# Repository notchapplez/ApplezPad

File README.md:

# ApplezPad

## PCB
Schematic

PCB

cat i drew myself, i am very proud .-.

I use kmk for the firmware.

I am just planning to mount my hackpad on this plate and it having a "naked" look.

## BOM:
- 9x Cherry MX Switches
- 6x DSA Keycaps
- 1x XIAO RP2040

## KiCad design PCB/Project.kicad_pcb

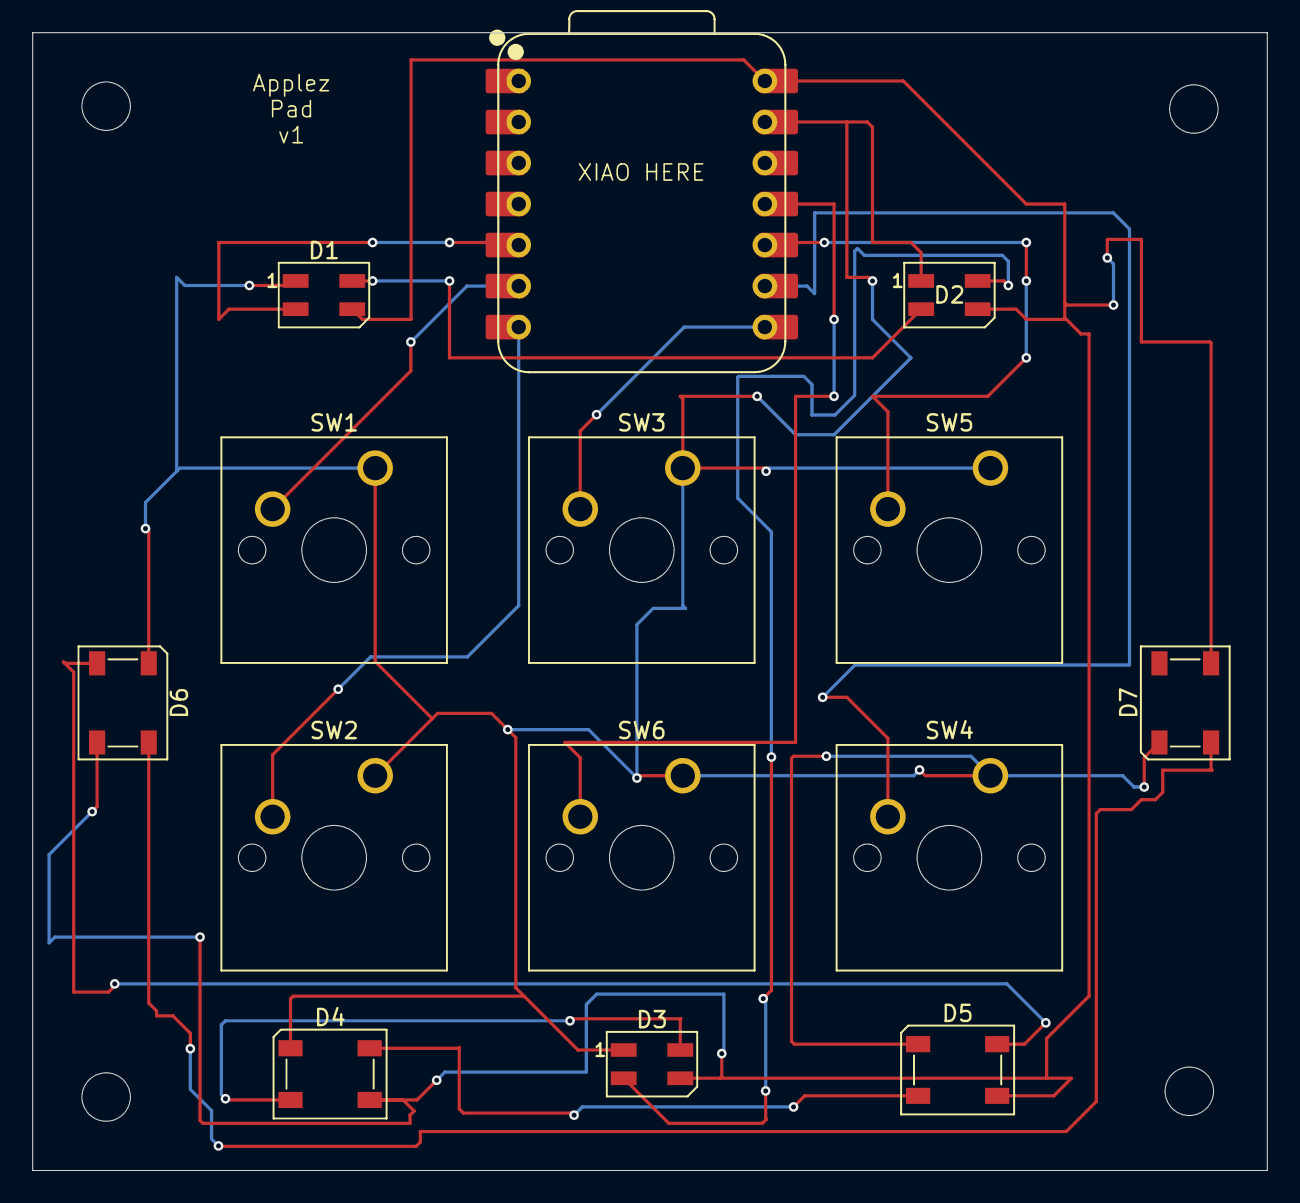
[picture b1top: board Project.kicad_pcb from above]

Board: 2 copper layers, 76.5 x 70.5 mm, 14 parts (0 on the bottom side), 15 nets.

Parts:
D1, D2, D3: SK6812; LED_SK6812MINI_PLCC4_3.5x3.5mm_P1.75mm
D4, D5, D6, D7: SK6812; LED_SK6812_PLCC4_5.0x5.0mm_P3.2mm
SW1, SW2, SW3, SW4, SW5, SW6: SW_Push; SW_Cherry_MX_1.00u_PCB
U1: XIAO-RP2040-DIP

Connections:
+5V: D1.3 (VDD), D2.3 (VDD), D3.3 (VDD), D4.3 (VDD), D5.3 (VDD), D6.3 (VDD), D7.3 (VDD), U1.14 (VBUS)
GND: D1.1 (VSS), D2.1 (VSS), D3.1 (VSS), D4.1 (VSS), D5.1 (VSS), D6.1 (VSS), D7.1 (VSS), SW1.1, SW2.1, SW3.1, SW4.1, SW5.1, SW6.1, U1.13 (GND)
unnamed: D1.2 (DIN), U1.5 (GPIO6/SDA)
unnamed: D1.4 (DOUT), D2.2 (DIN)
unnamed: D2.4 (DOUT), D3.2 (DIN)
unnamed: D3.4 (DOUT), D4.2 (DIN)
unnamed: D4.4 (DOUT), D5.2 (DIN)
unnamed: D5.4 (DOUT), D6.2 (DIN)
unnamed: D6.4 (DOUT), D7.2 (DIN)
unnamed: SW2.2, U1.7 (GPIO0/TX)
unnamed: SW3.2, U1.8 (GPIO1/RX)
unnamed: SW4.2, U1.9 (GPIO2/SCK)
unnamed: SW6.2, U1.11 (GPIO3/MOSI)
unnamed: SW5.2, U1.10 (GPIO4/MISO)
unnamed: SW1.2, U1.6 (GPIO7/SCL)

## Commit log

2025-06-07 Main commit
2025-11-14 Update README to remove CAD model and adjust PCB
    Removed CAD model image and updated PCB section.
2025-11-14 Revise schematic images and update BOM
    Updated schematic images and BOM details.
2025-11-14 Update main.py for keyboard and module integration
    Refactor keyboard setup and remove unused code.
2025-11-14 Add new file PCB/t with content 'as'
2025-11-16 meow
    meow meow mrrp add meowy cat
2025-11-16 Include cat drawing in README
    Added a personal touch with a cat drawing and image.
